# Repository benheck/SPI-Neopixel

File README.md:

# SPI-Neopixel
Circuit to convert 800kHz SPI bus mode 1 into WS2812 "Neopixel" pulse width data

/CS (chip select active low) allows you to have other things on the same SPI bus as this converter.

Tested in breadboard form to be working. Ordered PCB's using this board file from OSHpark. Will update when that has been tested.

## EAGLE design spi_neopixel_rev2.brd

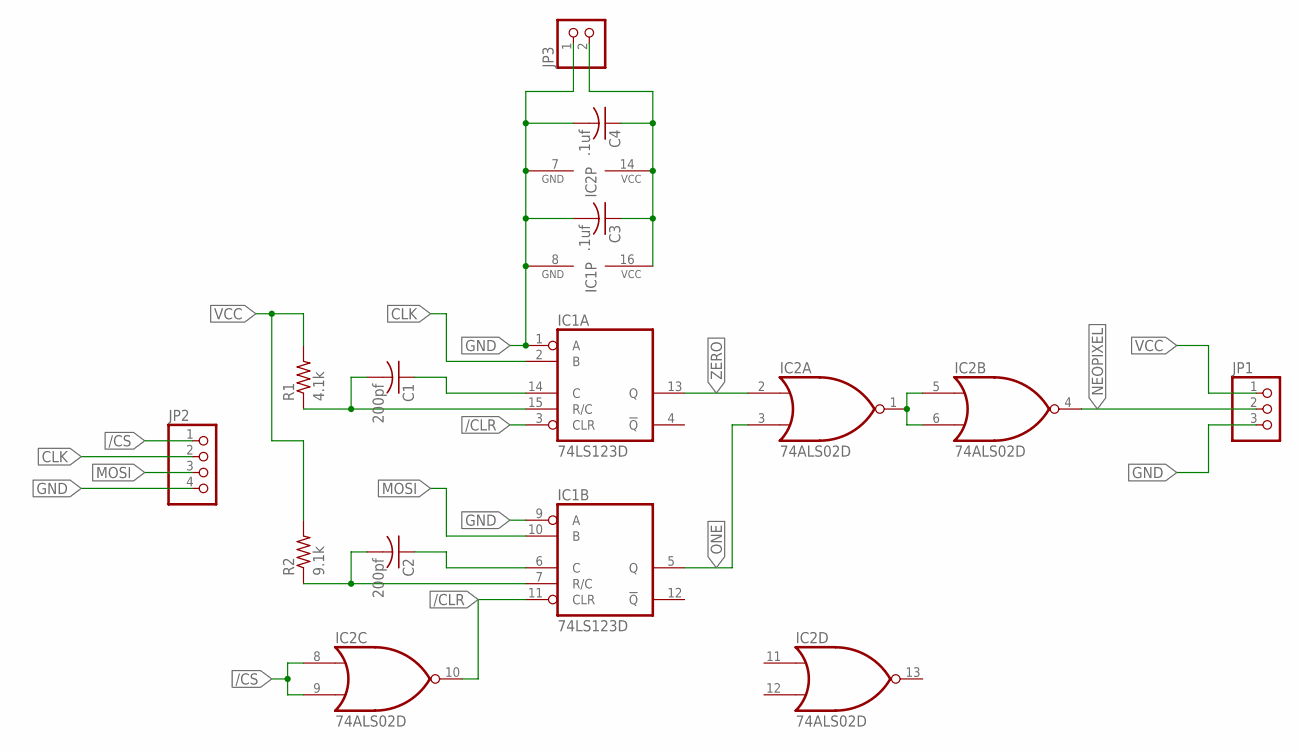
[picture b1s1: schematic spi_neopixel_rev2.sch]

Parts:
C1, C2: 200pf; C0805
C3, C4: .1uf; C0805
IC1: 74LS123D; SO16
IC2: 74ALS02D; SO14
JP1: PINHD-1X3; 1X03
JP2: PINHD-1X4; 1X04
JP3: PINHD-1X2; 1X02
R1: 4.1k; M0805
R2: 9.1k; M0805

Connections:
/CLR: IC1.3 (CLR), IC1.11 (CLR), IC2.10 (O)
/CS: IC2.8 (I0), IC2.9 (I1), JP2.1
CLK: IC1.2 (B), JP2.2
GND: C3.2, C4.2, IC1.1 (A), IC1.8 (GND), IC1.9 (A), IC2.7 (GND), JP1.3, JP2.4, JP3.1
MOSI: IC1.10 (B), JP2.3
unnamed: IC2.1 (O), IC2.5 (I0), IC2.6 (I1)
unnamed: C1.2, IC1.15 (R/C), R1.1
unnamed: C2.2, IC1.7 (R/C), R2.1
unnamed: C1.1, IC1.14 (C)
unnamed: C2.1, IC1.6 (C)
NEOPIXEL: IC2.4 (O), JP1.2
ONE: IC1.5 (Q), IC2.3 (I1)
VCC: C3.1, C4.1, IC1.16 (VCC), IC2.14 (VCC), JP1.1, JP3.2, R1.2, R2.2
ZERO: IC1.13 (Q), IC2.2 (I0)

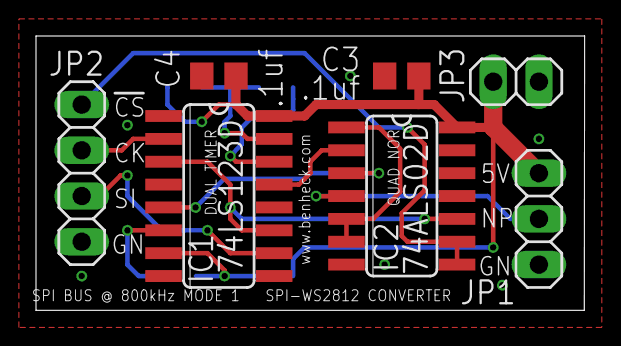
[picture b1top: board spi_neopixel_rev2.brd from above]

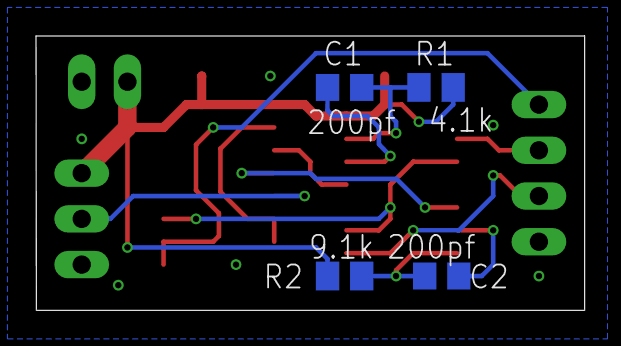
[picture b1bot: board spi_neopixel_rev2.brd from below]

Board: 2 copper layers, 30.5 x 15.2 mm, 11 parts (4 on the bottom side), 14 nets.
